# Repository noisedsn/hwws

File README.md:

# HWWS

A humble weather station project created few years ago just because I wanted to play in some different fields, from hardware design and programming in few different languages to UI-UX and graphics design.

## Web server

Simple PHP backend that allows managing users, adding multiple sensors, making them public or private (available only for logged in users). Serverless SQLite database was chosen for simplicity. To prevent flooding, sensors are authorized with a simple Digest-like authentication and must be paired using the PIN code issued by the server.

Front-end features a responsive design and multilangual support.

### Requirements: 
- PHP 8+
- php-sqlite3

### Installation:
- Copy all files from the "webserver" directory to your server.
- Make sure that directories "/assets/favicon/cache" and "/db" are writable.
- Navigate to the selected URL and complete the setup process.

During the installation, the first created user will receive Administrator rights and will be able to add new users and sensors. Non-admin users can only view the configuration and access private sensors.

Next, add a sensor. Station elevation (in meters) is required to recalculate local atmospheric pressure to standard sea-level pressure.

## Hardware

### For a bare minimum:

- Microcontroller - ESP8266 or ESP32-C3.
- Temperature, humidity and pressure sensor - BME280.

### Optional (battery, solar charging, battery monitoring, improved stability): 

- TP4056 + DW01A charging module
- 6V Solar panel
- Single cell Li-ion or Lipo battery
- Few other discrete components, to complete power circuits. D1 and D1 must be a Zener diodes with a low forward voltage drop.

PCB designs are single-sided, made in KiCad and optimized for DIY etching at home (but can be manufactured as well). The photo shows my prototyping board, etched from a laser-printed page using citric acid + hydrogen peroxide recipe.

## Firmware

Sensor firmware is fully configurable via built-in web interface. Developed using Arduino IDE.

### Pairing process:
After first flashing, the microcontroller's WiFi access point will be active immediately, allowing you to pair the sensor with the web server. Connect, using the following credentials:

- AP SSID: `Weather Sensor`
- Password: `123456789`
- Open in browser: `192.168.4.1`

Next, finish the sensor setup:
- Enter SSID and password of your WiFi network.
- Server URL (homepage) where the HWWS webserver was installed.
- PIN code issued by the server. It is used to authenticate and identify sensors. 

If you need to change the settings later, press the reset button twice within a second and it will enter pairing mode again.

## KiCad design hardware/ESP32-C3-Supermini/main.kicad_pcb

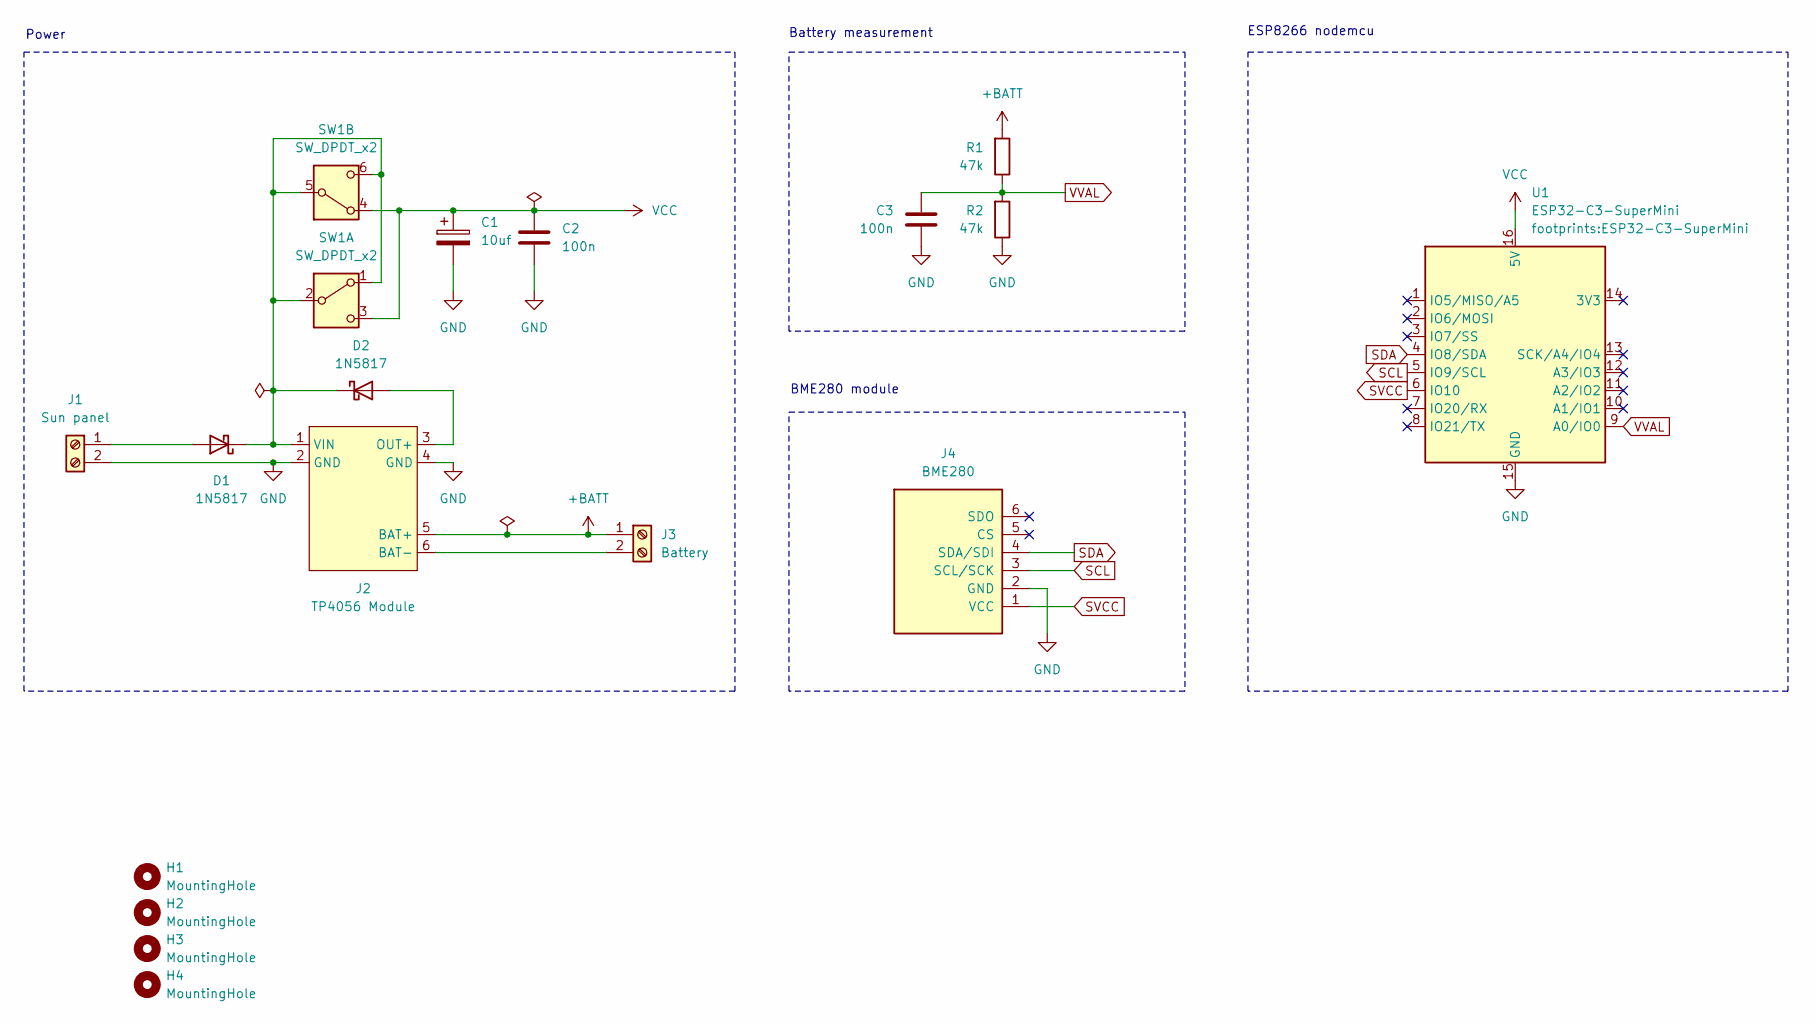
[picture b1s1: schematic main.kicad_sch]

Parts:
C1: 10uf; CP_Radial_D4.0mm_P2.00mm
C2, C3: 100n; C_0805_2012Metric
D1, D2: 1N5817; D_DO-41_SOD81_P10.16mm_Horizontal
H1, H2, H3, H4: MountingHole; MountingHole_2.5mm
J1: Sun panel; TerminalBlock_bornier-2_P5.08mm
J2: TP4056 Module; Charge_Controller_TP4056
J3: Battery; TerminalBlock_bornier-2_P5.08mm
J4: BME280; BME280 module
R1, R2: 47k; R_0805_2012Metric
SW1: SW_DPDT_x2
U1: ESP32-C3-SuperMini

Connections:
+BATT: J2.5 (BAT+), J3.1, R1.2
GND: C1.2, C2.2, C3.2, J1.2, J2.2 (GND), J2.4 (GND), J4.2 (GND), R2.1, U1.15 (GND)
unnamed: D1.2 (A), J1.1
unnamed: D1.1 (K), D2.1 (K), J2.1 (VIN), SW1.1 (A), SW1.2 (B), SW1.5 (B), SW1.6 (C)
unnamed: D2.2 (A), J2.3 (OUT+)
unnamed: J2.6 (BAT-), J3.2
SCL: J4.3 (SCL/SCK), U1.5 (IO9/SCL)
SDA: J4.4 (SDA/SDI), U1.4 (IO8/SDA)
SVCC: J4.1 (VCC), U1.6 (IO10)
VCC: C1.1, C2.1, SW1.3 (C), SW1.4 (A), U1.16 (5V)
VVAL: C3.1, R1.1, R2.2, U1.9 (A0/IO0)

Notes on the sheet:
ESP8266 nodemcu
BME280 module
Battery measurement
Power

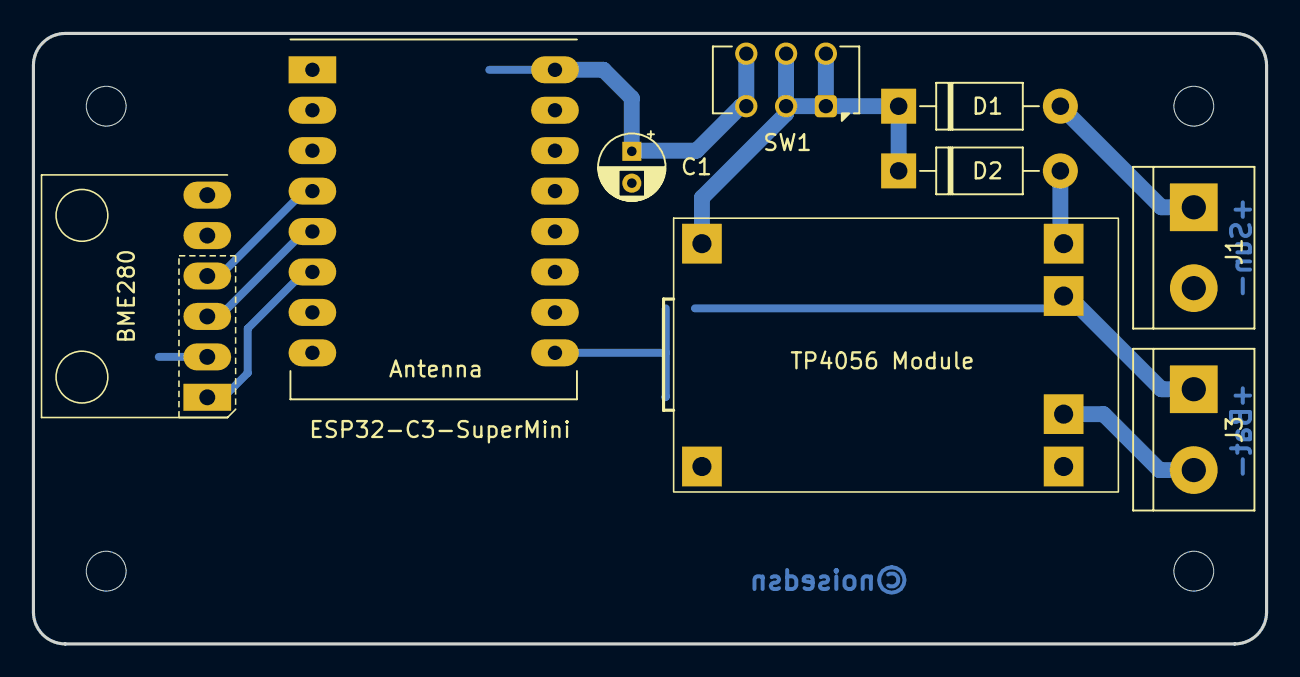
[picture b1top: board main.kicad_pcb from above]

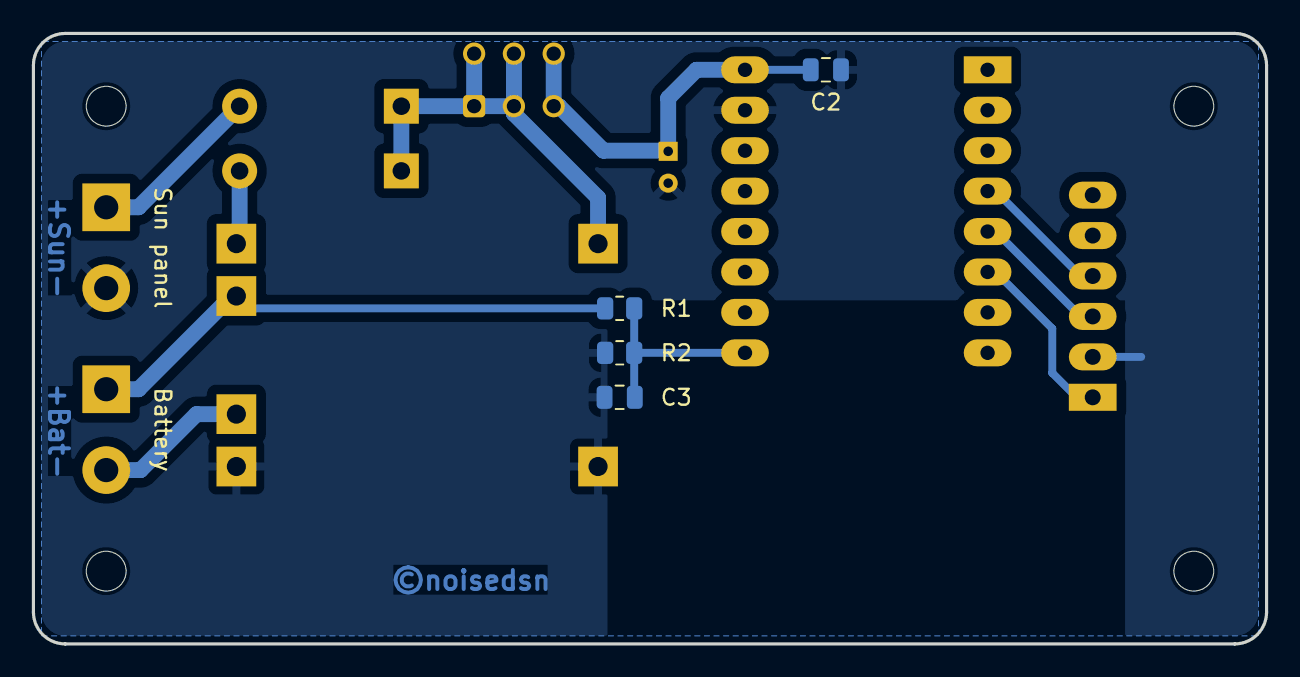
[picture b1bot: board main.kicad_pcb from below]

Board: 2 copper layers, 77.5 x 38.4 mm, 17 parts (4 on the bottom side), 11 nets.

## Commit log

2026-02-18 Cleaning old code
2026-02-18 Prevent background image caching
2026-02-18 Cleaning
2026-02-19 Loosing session fix
2026-02-20 Minor cleanup
2026-02-25 Update cookie to prolong session
2026-03-08 Cosmetic tweaks
2026-04-18 some cookie parameters changed

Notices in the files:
hardware/ESP32-C3-Supermini/main.kicad_pcb:
©noisedsn
